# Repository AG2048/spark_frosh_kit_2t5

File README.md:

# Spark Design Club F!rosh Kit 2T5
F!rosh kit PCB design and programming files for F!rosh 2T5.

# Description
The Spark F!rosh Kit 2T5 is a set of custom PCB designs featuring the Spark Design Club logo and branding. It is designed to act as a puzzle piece with two different color options. Each board of one colour can piece with two other boards of the other colour on two edges, and with 4 boards together, they form a loop in the shape of a large square!

This PCB features the ATTiny10 microcontroller, a small and versatile chip that can be easily powered, perfect for small, low-power applications like this F!rosh Kit PCB. Each board can communicate with the "downstream" board it is connected to and share power, with the ability to identify if the board itself has the "source power". 

The boards alone is a durable design for a keychain, showcasing your interest in electronics and design. When soldered, it can be used as a simple LED light source when powered. 

The real complex design of the boards comes into play when 4 soldered boards come together and form the larger square shape. When powered, these boards can be used to display more complex patterns!

The objective of this design is to make a cool-looking PCB, while also using its puzzle-like design to encourage F!rosh this year to meet new friends (reference: some old coca-cola commercial that did this...)

# File Structure
- `board_design_files/`: Contains the PCB design files for the F!rosh 2T5 kit. The BOM can also be found somewhere in this directory.
- `frosh_kit_program/`: Contains the Arduino program files for the F!rosh 2T5 kit.
- `imgs/`: Contains images related to the F!rosh 2T5 kit.
- `programming_resources/`: Contains resources for programming the ATTiny10 microcontroller. These files may be produced by other people. 

# Programming
The ATTiny10 microcontroller used in the F!rosh Kit can be programmed using the Tiny Programming Interface (TPI). The instruction to program the ATTiny10 using TPI was originally found on [this tutorial](https://make.kosakalab.com/make/electronic-work/arduio_tpi_en/). Unfortunately, as of September 1, 2025, this tutorial site is no longer available. Therefore, I have provided the necessary instructions below.

## Wire Connections
1. Prepare an Arduino UNO and 4 resistors (anywhere from 220Ω to 1kΩ should work).
2. Connect pin 10, 11, 12, and 13 of the Arduino UNO to the 4 resistors. Respectively, the other end of the resistors connected to pins 10, 11 and 12, and 13 represents `RESET`, `TPIDATA`, and `TPICLK`. (Image from the original tutorial)

3. Connect `RESET` to the `R` pin, `TPIDATA` to the `D` pin, and `TPICLK` to the `C` pin. Also connect 5V to `VIN` or `+` or `VCC`, and ground to `GND` or `-`. The pins are visible from the front of the board:

- Note, if it's hard to connect to the `R`, `C`, `D` pins, you can connect `TPIDATA` to the `DIN` pin, and connect the `TPICLK` to the `CLK` pin. 

## Programming Environment Setup
1. Download the [modified Arduino programmer](programming_resources/ATtiny4_5_9_10_20_40Programmer_2/) obtained from the original tutorial.
2. Using the Arduino IDE, upload this sketch to the Arduino UNO.
3. Copy the following package.json URL to the Arduino IDE's Additional Board Manager URLs: `https://raw.githubusercontent.com/AG2048/spark_frosh_kit_2t5/refs/heads/main/programming_resources/package_bitDuino10-arduinoTPI_index.json` and click `OK`. (The original json file link is [here](https://kimio-kosaka.github.io/bitDuino10-arduinoTPI/package_bitDuino10-arduinoTPI_index.json), but a bug fix was needed to make this work on newer versions of Arduino IDE / AVR Board Packages)
4. Go to Tools > Board > Boards Manager, search for `bitduino`, and install `bitDuino10-aTPI`.
5. In Tools > Board, select `ATtiny10(bitDuino10-arduinoTPI)` as the active board, and select the port that the Arduino UNO is connected to. 

## Programming the ATTiny10
1. Load the (F!rosh Kit Program)[frosh_kit_program/] into the Arduino IDE.
2. Click the "Upload" button. 

## Notes:
The original package had a bug with the avr-gcc compiler version. Originally, it has to be set to version `5.4.0-atmel3.6.1-arduino2`, which forces users to use Arduino IDE 1.8.9 or less and version 1.6.23 of the Arduino AVR Boards platform. Details of this bug can be found in this [issue thread](https://github.com/kimio-kosaka/bitDuino10-arduinoTPI/issues/4#issuecomment-1046231772). 

As a fix, I adopted the solution mentioned in the issue thread, and made my [own copy of the package json file](programming_resources/package_bitDuino10-arduinoTPI_index.json) that adds the following package dependency specifications:

```json
      "toolsDependencies": [
        {
          "packager": "arduino",
          "name": "avr-gcc",
          "version": "5.4.0-atmel3.6.1-arduino2"
        },
        {
          "packager": "bitDuino10-aTPI",
          "name": "avrboy",
          "version": "1.0.1"
        }
      ]
```

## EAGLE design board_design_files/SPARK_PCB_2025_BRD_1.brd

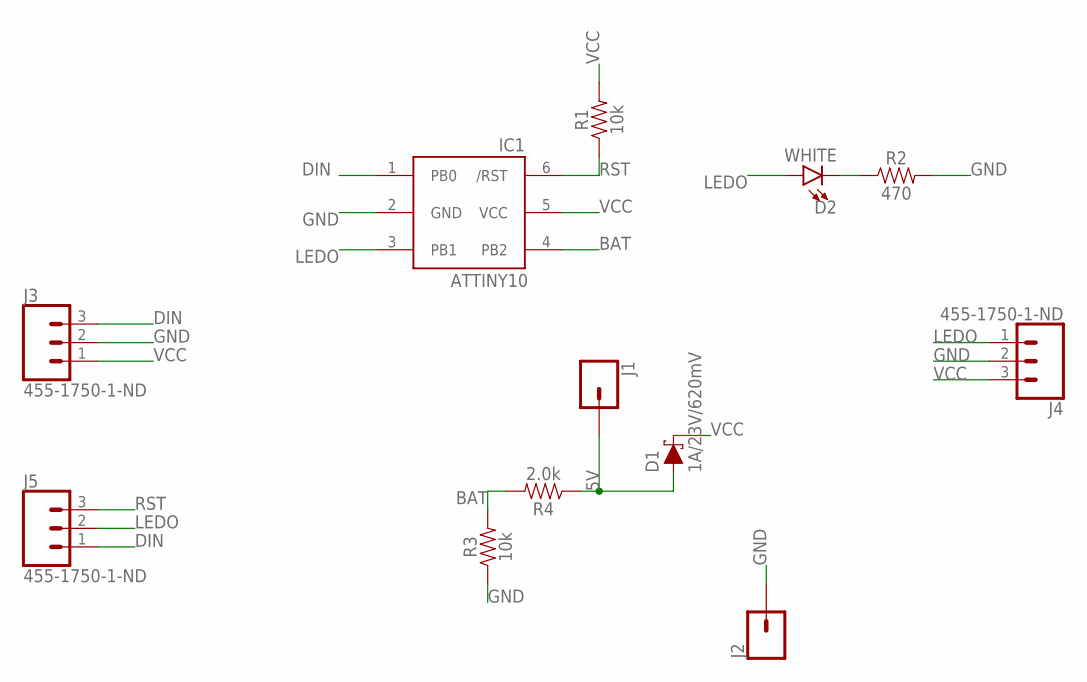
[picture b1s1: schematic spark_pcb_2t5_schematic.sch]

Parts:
D1: 1A/23V/620mV; SOD-323
D2: WHITE; LED-0603
IC1: ATTINY10; SOT23-6
J1, J2: CONN_01; 1X01
J3, J4, J5: 455-1750-1-ND; 1X03
R1, R3: 10k; 0603
R2: 470; 0603
R4: 2.0k; 0603

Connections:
5V: D1.A, J1.1, R4.1
BAT: IC1.4 (PB2), R3.2, R4.2
DIN: IC1.1 (PB0), J3.3, J5.1
GND: IC1.2 (GND), J2.1, J3.2, J4.2, R2.2, R3.1
LEDO: D2.A, IC1.3 (PB1), J4.1, J5.2
unnamed: D2.C, R2.1
RST: IC1.6 (/RST), J5.3, R1.1
VCC: D1.C, IC1.5 (VCC), J3.1, J4.3, R1.2

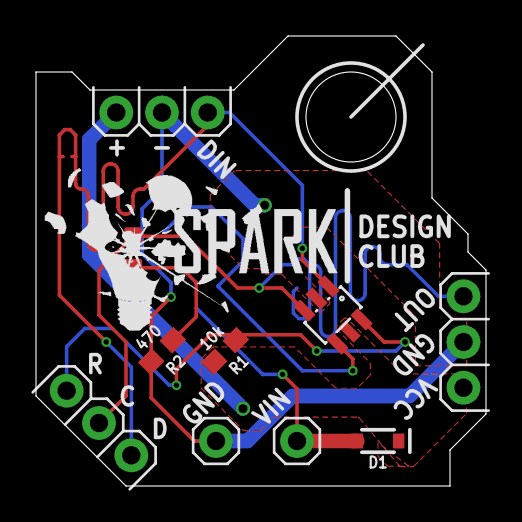
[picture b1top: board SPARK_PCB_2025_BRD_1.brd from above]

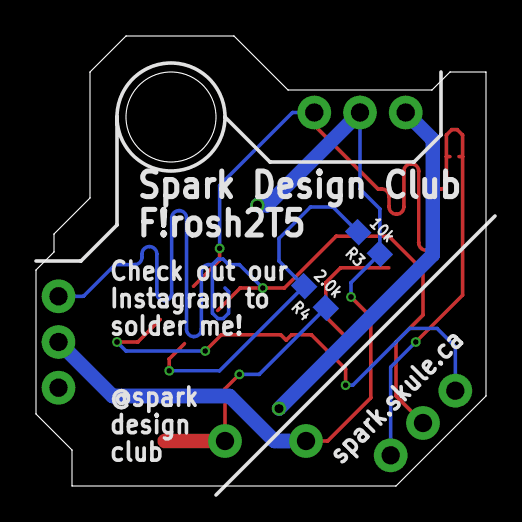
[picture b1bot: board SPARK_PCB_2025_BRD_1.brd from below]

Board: 2 copper layers, 25.0 x 25.0 mm, 12 parts (2 on the bottom side), 8 nets.

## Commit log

2025-09-02 Add bitDuino10-arduinoTPI package index
    Introduces package_bitDuino10-arduinoTPI_index.json for Arduino board and tool definitions, enabling support for ATtiny10(arduinoTPI) and avrboy tool across multiple platforms.
2025-09-02 Add SPARK PCB 2025 board and CAM files
    Initial commit of SPARK PCB 2025 board design files, including two board layouts, 3D models, CAM outputs (Gerber, drill, ODB, and assembly files), and schematic. This provides all necessary files for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
2025-09-02 Add board preview, produced board, and schematic images
    Added new images for board previews, produced boards, programming figures, renders, and schematics to support documentation and visualization of hardware and assembly processes.
2025-09-02 Add CERN OHL and GPL license files
    Added LICENSE-CERN (CERN Open Hardware Licence v2 - Strongly Reciprocal) and LICENSE-GPL (GNU General Public License v3) to clarify project licensing and terms of use.
2025-09-02 Add ATtiny TPI programmer Arduino sketch
    Initial commit of ATtiny4/5/9/10/20/40 programmer for Arduino, supporting TPI programming via serial commands. Includes memory dump, chip erase, program writing, fuse and lock bit management, device 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
2025-09-02 Update README with detailed project info and instructions
    Expanded the README to include a comprehensive description of the Spark F!rosh Kit 2T5, its features, file structure, and step-by-step programming instructions for the ATTiny10 microcontroller. Added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
2025-09-02 Add initial frosh kit PCB program
    Implements the main logic for the Spark Design Club 2T5 F!rosh PCB, including pin setup, main/secondary board detection, and output patterns based on board configuration. This is the initial version 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
2025-09-02 Update README.md
    Adding reminder to connect power when programming.
2025-09-02 Update README.md
    Clearer pin names in programming instruction
2025-09-02 Add delay to setup before turning light on
    Issue #1: Previously, some board may have completed the "has_prev" check too quickly, and begin turning itself on without allowing the next board to read its "off" state. Adding a long delay makes su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
2025-09-02 Resolve board not completing final cycle
    From Issue #2, there were no delay between the end of the toggle sequence to when the side boards first detect falling edges. This, in combination of the constant toggle behaviour for the toggle patt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
    This is resolved by adding a short delay after the toggle sequence, making sure
2025-09-03 #3 Fix increase delay duration
    Previous 800ms delay forgot to consider the duration the last LED should've been on as well. To make the timing consistent, last LED should also have a delay time of 250 ms. Thus making the delay aft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
2025-09-03 Update README with better programming instructions
    Clarified the programming section for the ATTiny10 microcontroller, corrected pin mappings, and added notes for alternative connections. Also updated the board design files description to mention the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

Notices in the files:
parts and their libraries:
SparkFun-Connectors: Licensing: Creative Commons ShareAlike 4.0 International - https://creativecommons.org/licenses/by-sa/4.0
